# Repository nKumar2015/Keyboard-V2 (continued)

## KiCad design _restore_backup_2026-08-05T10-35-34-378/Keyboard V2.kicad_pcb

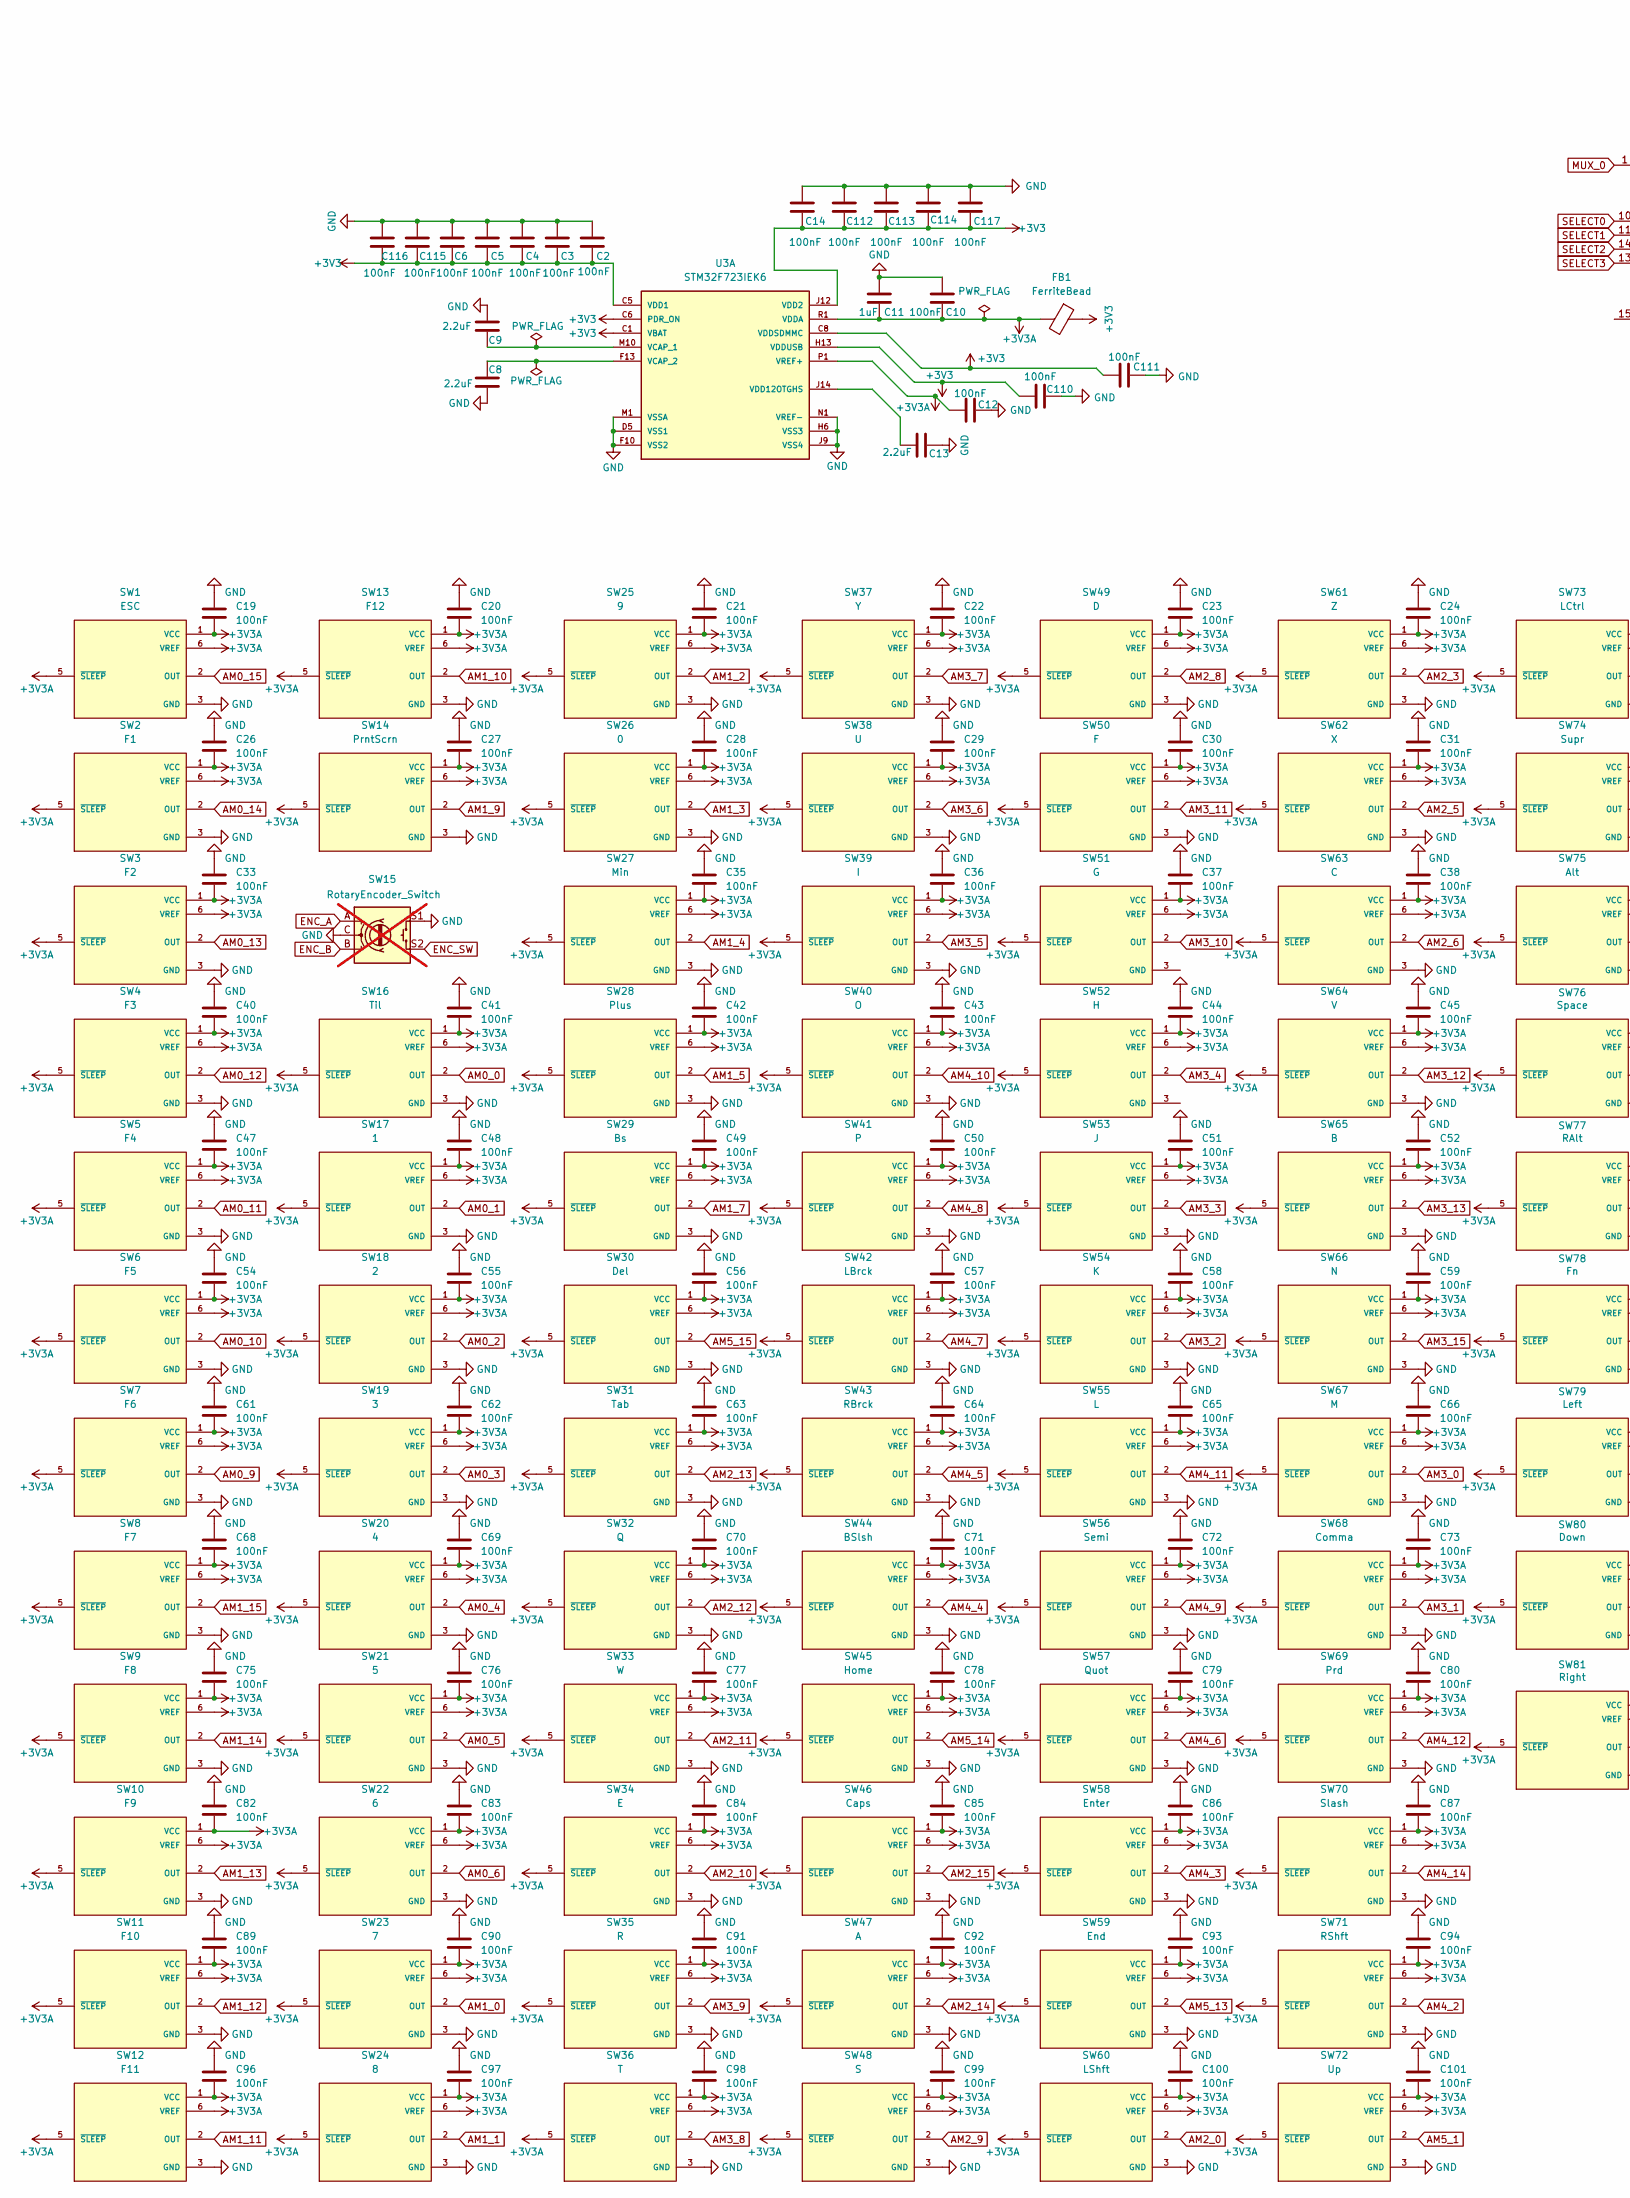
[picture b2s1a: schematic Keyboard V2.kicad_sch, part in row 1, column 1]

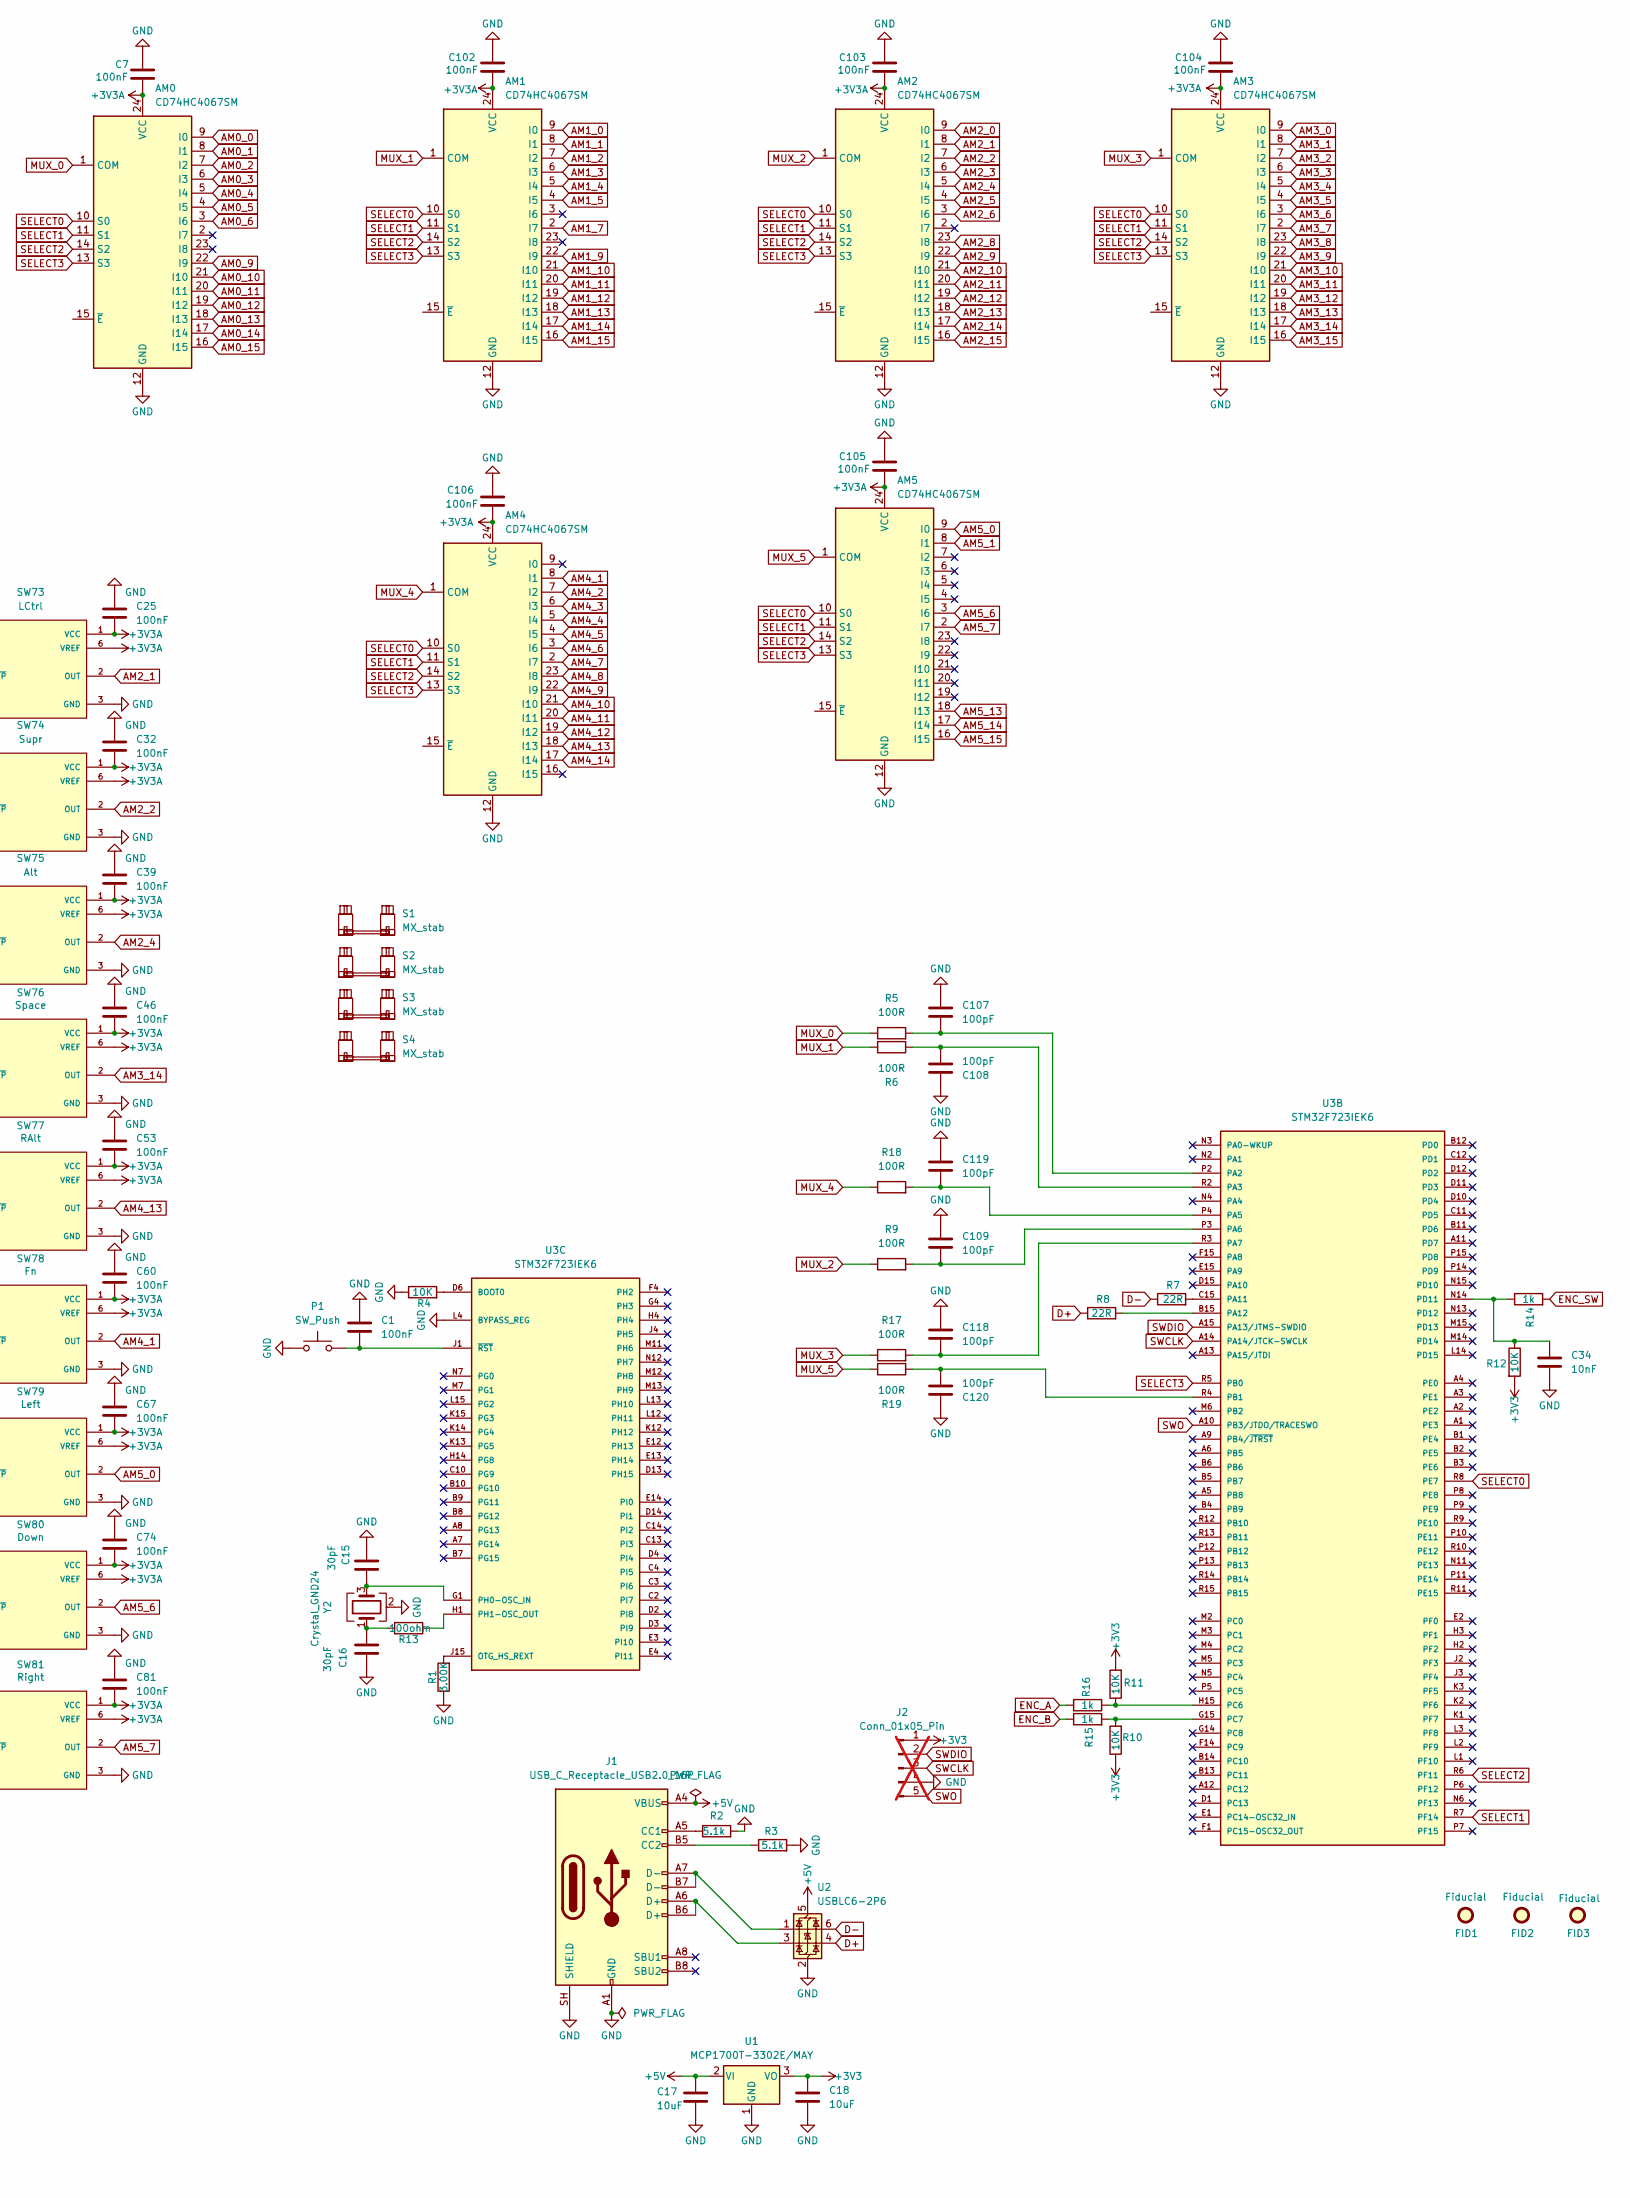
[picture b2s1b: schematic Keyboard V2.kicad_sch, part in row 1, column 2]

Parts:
AM0, AM1, AM2, AM3, AM4, AM5: CD74HC4067SM; SSOP-24_5.3x8.2mm_P0.65mm; LCSC C98457
C1, C7, C102, C103, C104, C105, C106: 100nF; C_0603_1608Metric
C2, C3, C4, C5, C6, C10, C12, C14, C19, C20, C21, C22, C23, C24, C25, C26, C27, C28, C29, C30, C31, C32, C33, C35, C36, C37, C38, C39, C40, C41, C42, C43, C44, C45, C46, C47, C48, C49, C50, C51, C52, C53, C54, C55, C56, C57, C58, C59, C60, C61, C62, C63, C64, C65, C66, C67, C68, C69, C70, C71, C72, C73, C74, C75, C76, C77, C78, C79, C80, C81, C82, C83, C84, C85, C86, C87, C89, C90, C91, C92, C93, C94, C96, C97, C98, C99, C100, C101, C110, C111, C112, C113, C114, C115, C116, C117: 100nF; C_0402_1005Metric
C8, C9, C13: 2.2uF; C_0402_1005Metric
C11: 1uF; C_0402_1005Metric
C15, C16: 30pF; C_0402_1005Metric
C17, C18: 10uF; C_0805_2012Metric
C34: 10nF; C_0402_1005Metric
C107, C108, C109, C118, C119, C120: 100pF; C_0402_1005Metric
FB1: FerriteBead; L_0603_1608Metric
FID1, FID2, FID3: Fiducial; Fiducial_1mm_Mask2mm
J1: USB_C_Receptacle_USB2.0_16P; USB_C_Receptacle_HRO_TYPE-C-31-M-12
J2: Conn_01x05_Pin; PinHeader_1x05_P2.54mm_Horizontal; not fitted
P1: SW_Push; SW_SPST_SKQG_WithStem
R1: 3.00K; R_0603_1608Metric
R2, R3: 5.1k; R_0603_1608Metric
R4, R12: 10K; R_0603_1608Metric
R5, R6, R9, R17, R18, R19: 100R; R_0402_1005Metric
R7, R8: 22R; R_0402_1005Metric
R10, R11: 10K; R_0402_1005Metric
R13: 100ohm; R_0603_1608Metric
R14: 1k; R_0603_1608Metric
R15, R16: 1k; R_0402_1005Metric
S1: MX_stab; STAB_MX_P_6.25u
S2: MX_stab; STAB_MX_2.25u
S3: MX_stab; STAB_MX_P_2.25u
S4: MX_stab; STAB_MX_P_2u
SW1: ESC; SW_MX_HE_0deg_1u_DFN; PARTREV 7; LCSC C146410
SW2: F1; SW_MX_HE_0deg_1u_DFN; PARTREV 7; LCSC C146410
SW3: F2; SW_MX_HE_0deg_1u_DFN; PARTREV 7; LCSC C146410
SW4: F3; SW_MX_HE_0deg_1u_DFN; PARTREV 7; LCSC C146410
SW5: F4; SW_MX_HE_0deg_1u_DFN; PARTREV 7; LCSC C146410
SW6: F5; SW_MX_HE_0deg_1u_DFN; PARTREV 7; LCSC C146410
SW7: F6; SW_MX_HE_0deg_1u_DFN; PARTREV 7; LCSC C146410
SW8: F7; SW_MX_HE_0deg_1u_DFN; PARTREV 7; LCSC C146410
SW9: F8; SW_MX_HE_0deg_1u_DFN; PARTREV 7; LCSC C146410
SW10: F9; SW_MX_HE_0deg_1u_DFN; PARTREV 7; LCSC C146410
SW11: F10; SW_MX_HE_0deg_1u_DFN; PARTREV 7; LCSC C146410
SW12: F11; SW_MX_HE_0deg_1u_DFN; PARTREV 7; LCSC C146410
SW13: F12; SW_MX_HE_0deg_1u_DFN; PARTREV 7; LCSC C146410
SW14: PrntScrn; SW_MX_HE_0deg_1u_DFN; PARTREV 7; LCSC C146410
SW15: RotaryEncoder_Switch; ROT_Alps_EC11E-Switch; not fitted
SW16: Til; SW_MX_HE_0deg_1u_DFN; PARTREV 7; LCSC C146410
SW17: 1; SW_MX_HE_0deg_1u_DFN; PARTREV 7; LCSC C146410
SW18: 2; SW_MX_HE_0deg_1u_DFN; PARTREV 7; LCSC C146410
SW19: 3; SW_MX_HE_0deg_1u_DFN; PARTREV 7; LCSC C146410
SW20: 4; SW_MX_HE_0deg_1u_DFN; PARTREV 7; LCSC C146410
SW21: 5; SW_MX_HE_0deg_1u_DFN; PARTREV 7; LCSC C146410
SW22: 6; SW_MX_HE_0deg_1u_DFN; PARTREV 7; LCSC C146410
SW23: 7; SW_MX_HE_0deg_1u_DFN; PARTREV 7; LCSC C146410
SW24: 8; SW_MX_HE_0deg_1u_DFN; PARTREV 7; LCSC C146410
SW25: 9; SW_MX_HE_0deg_1u_DFN; PARTREV 7; LCSC C146410
SW26: 0; SW_MX_HE_0deg_1u_DFN; PARTREV 7; LCSC C146410
SW27: Min; SW_MX_HE_0deg_1u_DFN; PARTREV 7; LCSC C146410
SW28: Plus; SW_MX_HE_0deg_1u_DFN; PARTREV 7; LCSC C146410
SW29: Bs; SW_MX_HE_0deg_1u_DFN; PARTREV 7; LCSC C146410
SW30: Del; SW_MX_HE_0deg_1u_DFN; PARTREV 7; LCSC C146410
SW31: Tab; SW_MX_HE_0deg_1u_DFN; PARTREV 7; LCSC C146410
SW32: Q; SW_MX_HE_0deg_1u_DFN; PARTREV 7; LCSC C146410
SW33: W; SW_MX_HE_0deg_1u_DFN; PARTREV 7; LCSC C146410
SW34: E; SW_MX_HE_0deg_1u_DFN; PARTREV 7; LCSC C146410
SW35: R; SW_MX_HE_0deg_1u_DFN; PARTREV 7; LCSC C146410
SW36: T; SW_MX_HE_0deg_1u_DFN; PARTREV 7; LCSC C146410
SW37: Y; SW_MX_HE_0deg_1u_DFN; PARTREV 7; LCSC C146410
SW38: U; SW_MX_HE_0deg_1u_DFN; PARTREV 7; LCSC C146410
SW39: I; SW_MX_HE_0deg_1u_DFN; PARTREV 7; LCSC C146410
SW40: O; SW_MX_HE_0deg_1u_DFN; PARTREV 7; LCSC C146410
SW41: P; SW_MX_HE_0deg_1u_DFN; PARTREV 7; LCSC C146410
SW42: LBrck; SW_MX_HE_0deg_1u_DFN; PARTREV 7; LCSC C146410
SW43: RBrck; SW_MX_HE_0deg_1u_DFN; PARTREV 7; LCSC C146410
SW44: BSlsh; SW_MX_HE_0deg_1u_DFN; PARTREV 7; LCSC C146410
SW45: Home; SW_MX_HE_0deg_1u_DFN; PARTREV 7; LCSC C146410
SW46: Caps; SW_MX_HE_0deg_1u_DFN; PARTREV 7; LCSC C146410
SW47: A; SW_MX_HE_0deg_1u_DFN; PARTREV 7; LCSC C146410
SW48: S; SW_MX_HE_0deg_1u_DFN; PARTREV 7; LCSC C146410
SW49: D; SW_MX_HE_0deg_1u_DFN; PARTREV 7; LCSC C146410
SW50: F; SW_MX_HE_0deg_1u_DFN; PARTREV 7; LCSC C146410
SW51: G; SW_MX_HE_0deg_1u_DFN; PARTREV 7; LCSC C146410
SW52: H; SW_MX_HE_0deg_1u_DFN; PARTREV 7; LCSC C146410
SW53: J; SW_MX_HE_0deg_1u_DFN; PARTREV 7; LCSC C146410
SW54: K; SW_MX_HE_0deg_1u_DFN; PARTREV 7; LCSC C146410
SW55: L; SW_MX_HE_0deg_1u_DFN; PARTREV 7; LCSC C146410
SW56: Semi; SW_MX_HE_0deg_1u_DFN; PARTREV 7; LCSC C146410
SW57: Quot; SW_MX_HE_0deg_1u_DFN; PARTREV 7; LCSC C146410
SW58: Enter; SW_MX_HE_0deg_1u_DFN; PARTREV 7; LCSC C146410
SW59: End; SW_MX_HE_0deg_1u_DFN; PARTREV 7; LCSC C146410
SW60: LShft; SW_MX_HE_0deg_1u_DFN; PARTREV 7; LCSC C146410
SW61: Z; SW_MX_HE_0deg_1u_DFN; PARTREV 7; LCSC C146410
SW62: X; SW_MX_HE_0deg_1u_DFN; PARTREV 7; LCSC C146410
SW63: C; SW_MX_HE_0deg_1u_DFN; PARTREV 7; LCSC C146410
SW64: V; SW_MX_HE_0deg_1u_DFN; PARTREV 7; LCSC C146410
SW65: B; SW_MX_HE_0deg_1u_DFN; PARTREV 7; LCSC C146410
SW66: N; SW_MX_HE_0deg_1u_DFN; PARTREV 7; LCSC C146410
SW67: M; SW_MX_HE_0deg_1u_DFN; PARTREV 7; LCSC C146410
SW68: Comma; SW_MX_HE_0deg_1u_DFN; PARTREV 7; LCSC C146410
SW69: Prd; SW_MX_HE_0deg_1u_DFN; PARTREV 7; LCSC C146410
SW70: Slash; SW_MX_HE_0deg_1u_DFN; PARTREV 7; LCSC C146410
SW71: RShft; SW_MX_HE_0deg_1u_DFN; PARTREV 7; LCSC C146410
SW72: Up; SW_MX_HE_0deg_1u_DFN; PARTREV 7; LCSC C146410
SW73: LCtrl; SW_MX_HE_0deg_1u_DFN; PARTREV 7; LCSC C146410
SW74: Supr; SW_MX_HE_0deg_1u_DFN; PARTREV 7; LCSC C146410
SW75: Alt; SW_MX_HE_0deg_1u_DFN; PARTREV 7; LCSC C146410
SW76: Space; SW_MX_HE_0deg_1u_DFN; PARTREV 7; LCSC C146410
SW77: RAlt; SW_MX_HE_0deg_1u_DFN; PARTREV 7; LCSC C146410
SW78: Fn; SW_MX_HE_0deg_1u_DFN; PARTREV 7; LCSC C146410
SW79: Left; SW_MX_HE_0deg_1u_DFN; PARTREV 7; LCSC C146410
SW80: Down; SW_MX_HE_0deg_1u_DFN; PARTREV 7; LCSC C146410
SW81: Right; SW_MX_HE_0deg_1u_DFN; PARTREV 7; LCSC C146410
U1: MCP1700T-3302E/MAY; DFN-6-1EP_2x2mm_P0.65mm_EP1x1.6mm
U2: USBLC6-2P6; SOT-666
U3: STM32F723IEK6; IC_STM32F723IEK6; PARTREV 9
Y2: Crystal_GND24; Crystal_SMD_Abracon_ABM8G-4Pin_3.2x2.5mm

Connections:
+3V3: C2.1, C3.2, C4.2, C5.2, C6.2, C14.1, C18.1, C110.2, C111.1, C112.1, C113.1, C114.1, C115.2, C116.1, C117.1, FB1.1, J2.1, R10.1, R11.2, R12.2, U1.3 (VO), U3.C1 (VBAT), U3.C5 (VDD1), U3.C6 (PDR_ON), U3.C7 (VDD1), U3.C8 (VDDSDMMC), U3.C9 (VDD1), U3.F3 (VDD1), U3.G3 (VDD1), U3.G13 (VDD1), U3.H13 (VDDUSB), U3.J12 (VDD2), U3.J13 (VDD2), U3.K4 (VDD2), U3.N8 (VDD2), U3.N9 (VDD2), U3.N10 (VDD2)
+3V3A: AM0.24 (VCC), AM1.24 (VCC), AM2.24 (VCC), AM3.24 (VCC), AM4.24 (VCC), AM5.24 (VCC), C7.2, C10.2, C11.2, C12.2, C19.2, C20.2, C21.2, C22.2, C23.2, C24.2, C25.2, C26.2, C27.2, C28.2, C29.2, C30.2, C31.2, C32.2, C33.2, C35.2, C36.2, C37.2, C38.2, C39.2, C40.2, C41.2, C42.2, C43.2, C44.2, C45.2, C46.2, C47.2, C48.2, C49.2, C50.2, C51.2, C52.2, C53.2, C54.2, C55.2, C56.2, C57.2, C58.2, C59.2, C60.2, C61.2, C62.2, C63.2, C64.2, C65.2, C66.2, C67.2, C68.2, C69.2, C70.2, C71.2, C72.2, C73.2, C74.2, C75.2, C76.2, C77.2, C78.2, C79.2, C80.2, C81.2, C82.2, C83.2, C84.2, C85.2, C86.2, C87.2, C89.2, C90.2, C91.2, C92.2, C93.2, C94.2, C96.2, C97.2, C98.2, C99.2, C100.2, C101.2, C102.2, C103.2, C104.2, C105.2, C106.2, FB1.2, SW1.1 (VCC), SW1.5 (~SLEEP), SW1.6 (VREF), SW2.1 (VCC), SW2.5 (~SLEEP), SW2.6 (VREF), SW3.1 (VCC), SW3.5 (~SLEEP), SW3.6 (VREF), SW4.1 (VCC), SW4.5 (~SLEEP), SW4.6 (VREF), SW5.1 (VCC), SW5.5 (~SLEEP), SW5.6 (VREF), SW6.1 (VCC), SW6.5 (~SLEEP), SW6.6 (VREF), SW7.1 (VCC), SW7.5 (~SLEEP), SW7.6 (VREF), SW8.1 (VCC), SW8.5 (~SLEEP), SW8.6 (VREF), SW9.1 (VCC), SW9.5 (~SLEEP), SW9.6 (VREF), SW10.1 (VCC), SW10.5 (~SLEEP), SW10.6 (VREF), SW11.1 (VCC), SW11.5 (~SLEEP), SW11.6 (VREF), SW12.1 (VCC), SW12.5 (~SLEEP), SW12.6 (VREF), SW13.1 (VCC), SW13.5 (~SLEEP), SW13.6 (VREF), SW14.1 (VCC), SW14.5 (~SLEEP), SW14.6 (VREF), SW16.1 (VCC), SW16.5 (~SLEEP), SW16.6 (VREF), SW17.1 (VCC), SW17.5 (~SLEEP), SW17.6 (VREF), SW18.1 (VCC), SW18.5 (~SLEEP), SW18.6 (VREF), SW19.1 (VCC), SW19.5 (~SLEEP), SW19.6 (VREF), SW20.1 (VCC), SW20.5 (~SLEEP), SW20.6 (VREF), SW21.1 (VCC), SW21.5 (~SLEEP), SW21.6 (VREF), SW22.1 (VCC), SW22.5 (~SLEEP), SW22.6 (VREF), SW23.1 (VCC), SW23.5 (~SLEEP), SW23.6 (VREF), SW24.1 (VCC), SW24.5 (~SLEEP), SW24.6 (VREF), SW25.1 (VCC), SW25.5 (~SLEEP), SW25.6 (VREF), SW26.1 (VCC), SW26.5 (~SLEEP), SW26.6 (VREF), SW27.1 (VCC), SW27.5 (~SLEEP), SW27.6 (VREF), SW28.1 (VCC), SW28.5 (~SLEEP), SW28.6 (VREF), SW29.1 (VCC), SW29.5 (~SLEEP), SW29.6 (VREF), SW30.1 (VCC), SW30.5 (~SLEEP), SW30.6 (VREF), SW31.1 (VCC), SW31.5 (~SLEEP), SW31.6 (VREF), SW32.1 (VCC), SW32.5 (~SLEEP), SW32.6 (VREF), SW33.1 (VCC), SW33.5 (~SLEEP), SW33.6 (VREF), SW34.1 (VCC), SW34.5 (~SLEEP), SW34.6 (VREF), SW35.1 (VCC), SW35.5 (~SLEEP), SW35.6 (VREF), SW36.1 (VCC), SW36.5 (~SLEEP), SW36.6 (VREF), SW37.1 (VCC), SW37.5 (~SLEEP), SW37.6 (VREF), SW38.1 (VCC), SW38.5 (~SLEEP), SW38.6 (VREF), SW39.1 (VCC), SW39.5 (~SLEEP), SW39.6 (VREF), SW40.1 (VCC), SW40.5 (~SLEEP), SW40.6 (VREF), SW41.1 (VCC), SW41.5 (~SLEEP), SW41.6 (VREF), SW42.1 (VCC), SW42.5 (~SLEEP), SW42.6 (VREF), SW43.1 (VCC), SW43.5 (~SLEEP), SW43.6 (VREF), SW44.1 (VCC), SW44.5 (~SLEEP), SW44.6 (VREF), SW45.1 (VCC), SW45.5 (~SLEEP), SW45.6 (VREF), SW46.1 (VCC), SW46.5 (~SLEEP), SW46.6 (VREF), SW47.1 (VCC), SW47.5 (~SLEEP), SW47.6 (VREF), SW48.1 (VCC), SW48.5 (~SLEEP), SW48.6 (VREF), SW49.1 (VCC), SW49.5 (~SLEEP), SW49.6 (VREF), SW50.1 (VCC), SW50.5 (~SLEEP), SW50.6 (VREF), SW51.1 (VCC), SW51.5 (~SLEEP), SW51.6 (VREF), SW52.1 (VCC), SW52.5 (~SLEEP), SW52.6 (VREF), SW53.1 (VCC), SW53.5 (~SLEEP), SW53.6 (VREF), SW54.1 (VCC), SW54.5 (~SLEEP), SW54.6 (VREF), SW55.1 (VCC), SW55.5 (~SLEEP), SW55.6 (VREF), SW56.1 (VCC), SW56.5 (~SLEEP), SW56.6 (VREF), SW57.1 (VCC), SW57.5 (~SLEEP), SW57.6 (VREF), SW58.1 (VCC), SW58.5 (~SLEEP), SW58.6 (VREF), SW59.1 (VCC), SW59.5 (~SLEEP), SW59.6 (VREF), SW60.1 (VCC), SW60.5 (~SLEEP), SW60.6 (VREF), SW61.1 (VCC), SW61.5 (~SLEEP), SW61.6 (VREF), SW62.1 (VCC), SW62.5 (~SLEEP), SW62.6 (VREF), SW63.1 (VCC), SW63.5 (~SLEEP), SW63.6 (VREF), SW64.1 (VCC), SW64.5 (~SLEEP), SW64.6 (VREF), SW65.1 (VCC), SW65.5 (~SLEEP), SW65.6 (VREF), SW66.1 (VCC), SW66.5 (~SLEEP), SW66.6 (VREF), SW67.1 (VCC), SW67.5 (~SLEEP), SW67.6 (VREF), SW68.1 (VCC), SW68.5 (~SLEEP), SW68.6 (VREF), SW69.1 (VCC), SW69.5 (~SLEEP), SW69.6 (VREF), SW70.1 (VCC), SW70.5 (~SLEEP), SW70.6 (VREF), SW71.1 (VCC), SW71.5 (~SLEEP), SW71.6 (VREF), SW72.1 (VCC), SW72.5 (~SLEEP), SW72.6 (VREF), SW73.1 (VCC), SW73.5 (~SLEEP), SW73.6 (VREF), SW74.1 (VCC), SW74.5 (~SLEEP), SW74.6 (VREF), SW75.1 (VCC), SW75.5 (~SLEEP), SW75.6 (VREF), SW76.1 (VCC), SW76.5 (~SLEEP), SW76.6 (VREF), SW77.1 (VCC), SW77.5 (~SLEEP), SW77.6 (VREF), SW78.1 (VCC), SW78.5 (~SLEEP), SW78.6 (VREF), SW79.1 (VCC), SW79.5 (~SLEEP), SW79.6 (VREF), SW80.1 (VCC), SW80.5 (~SLEEP), SW80.6 (VREF), SW81.1 (VCC), SW81.5 (~SLEEP), SW81.6 (VREF), U3.P1 (VREF+), U3.R1 (VDDA)
+5V: C17.1, J1.A4 (VBUS), J1.A9 (VBUS), J1.B4 (VBUS), J1.B9 (VBUS), U1.2 (VI), U2.5 (VBUS)
AM0_0: AM0.9 (I0), SW16.2 (OUT)
AM0_1: AM0.8 (I1), SW17.2 (OUT)
AM0_2: AM0.7 (I2), SW18.2 (OUT)
AM0_3: AM0.6 (I3), SW19.2 (OUT)
AM0_4: AM0.5 (I4), SW20.2 (OUT)
AM0_5: AM0.4 (I5), SW21.2 (OUT)
AM0_6: AM0.3 (I6), SW22.2 (OUT)
AM0_9: AM0.22 (I9), SW7.2 (OUT)
AM0_10: AM0.21 (I10), SW6.2 (OUT)
AM0_11: AM0.20 (I11), SW5.2 (OUT)
AM0_12: AM0.19 (I12), SW4.2 (OUT)
AM0_13: AM0.18 (I13), SW3.2 (OUT)
AM0_14: AM0.17 (I14), SW2.2 (OUT)
AM0_15: AM0.16 (I15), SW1.2 (OUT)
AM1_0: AM1.9 (I0), SW23.2 (OUT)
AM1_1: AM1.8 (I1), SW24.2 (OUT)
AM1_2: AM1.7 (I2), SW25.2 (OUT)
AM1_3: AM1.6 (I3), SW26.2 (OUT)
AM1_4: AM1.5 (I4), SW27.2 (OUT)
AM1_5: AM1.4 (I5), SW28.2 (OUT)
AM1_7: AM1.2 (I7), SW29.2 (OUT)
AM1_9: AM1.22 (I9), SW14.2 (OUT)
AM1_10: AM1.21 (I10), SW13.2 (OUT)
AM1_11: AM1.20 (I11), SW12.2 (OUT)
AM1_12: AM1.19 (I12), SW11.2 (OUT)
AM1_13: AM1.18 (I13), SW10.2 (OUT)
AM1_14: AM1.17 (I14), SW9.2 (OUT)
AM1_15: AM1.16 (I15), SW8.2 (OUT)
AM2_0: AM2.9 (I0), SW60.2 (OUT)
AM2_1: AM2.8 (I1), SW73.2 (OUT)
AM2_2: AM2.7 (I2), SW74.2 (OUT)
AM2_3: AM2.6 (I3), SW61.2 (OUT)
AM2_4: AM2.5 (I4), SW75.2 (OUT)
AM2_5: AM2.4 (I5), SW62.2 (OUT)
AM2_6: AM2.3 (I6), SW63.2 (OUT)
AM2_8: AM2.23 (I8), SW49.2 (OUT)
AM2_9: AM2.22 (I9), SW48.2 (OUT)
AM2_10: AM2.21 (I10), SW34.2 (OUT)
AM2_11: AM2.20 (I11), SW33.2 (OUT)
AM2_12: AM2.19 (I12), SW32.2 (OUT)
AM2_13: AM2.18 (I13), SW31.2 (OUT)
AM2_14: AM2.17 (I14), SW47.2 (OUT)
AM2_15: AM2.16 (I15), SW46.2 (OUT)
AM3_0: AM3.9 (I0), SW67.2 (OUT)
AM3_1: AM3.8 (I1), SW68.2 (OUT)
AM3_2: AM3.7 (I2), SW54.2 (OUT)
AM3_3: AM3.6 (I3), SW53.2 (OUT)
AM3_4: AM3.5 (I4), SW52.2 (OUT)
AM3_5: AM3.4 (I5), SW39.2 (OUT)
AM3_6: AM3.3 (I6), SW38.2 (OUT)
AM3_7: AM3.2 (I7), SW37.2 (OUT)
AM3_8: AM3.23 (I8), SW36.2 (OUT)
AM3_9: AM3.22 (I9), SW35.2 (OUT)
AM3_10: AM3.21 (I10), SW51.2 (OUT)
AM3_11: AM3.20 (I11), SW50.2 (OUT)
AM3_12: AM3.19 (I12), SW64.2 (OUT)
AM3_13: AM3.18 (I13), SW65.2 (OUT)
AM3_14: AM3.17 (I14), SW76.2 (OUT)
AM3_15: AM3.16 (I15), SW66.2 (OUT)
AM4_1: AM4.8 (I1), SW78.2 (OUT)
AM4_2: AM4.7 (I2), SW71.2 (OUT)
AM4_3: AM4.6 (I3), SW58.2 (OUT)
AM4_4: AM4.5 (I4), SW44.2 (OUT)
AM4_5: AM4.4 (I5), SW43.2 (OUT)
AM4_6: AM4.3 (I6), SW57.2 (OUT)
AM4_7: AM4.2 (I7), SW42.2 (OUT)
AM4_8: AM4.23 (I8), SW41.2 (OUT)
AM4_9: AM4.22 (I9), SW56.2 (OUT)
AM4_10: AM4.21 (I10), SW40.2 (OUT)
AM4_11: AM4.20 (I11), SW55.2 (OUT)
AM4_12: AM4.19 (I12), SW69.2 (OUT)
AM4_13: AM4.18 (I13), SW77.2 (OUT)
AM4_14: AM4.17 (I14), SW70.2 (OUT)
AM5_0: AM5.9 (I0), SW79.2 (OUT)
AM5_1: AM5.8 (I1), SW72.2 (OUT)
AM5_6: AM5.3 (I6), SW80.2 (OUT)
AM5_7: AM5.2 (I7), SW81.2 (OUT)
AM5_13: AM5.18 (I13), SW59.2 (OUT)
AM5_14: AM5.17 (I14), SW45.2 (OUT)
AM5_15: AM5.16 (I15), SW30.2 (OUT)
D+: R8.1, U2.4 (I/O2)
D-: R7.1, U2.6 (I/O1)
ENC_A: R16.2, SW15.A
ENC_B: R15.1, SW15.B
ENC_SW: R14.2, SW15.S2
MUX_0: AM0.1 (COM), R5.1
MUX_1: AM1.1 (COM), R6.1
MUX_2: AM2.1 (COM), R9.1
MUX_3: AM3.1 (COM), R17.1
MUX_4: AM4.1 (COM), R18.1
MUX_5: AM5.1 (COM), R19.1
unnamed: C16.1, R13.2, Y2.1
unnamed: J1.A5 (CC1), R2.1
unnamed: J1.B5 (CC2), R3.1
unnamed: J1.A6 (D+), J1.B6 (D+), U2.3 (I/O2)
unnamed: J1.A7 (D-), J1.B7 (D-), U2.1 (I/O1)
unnamed: C9.1, U3.M10 (VCAP_1)
unnamed: C8.2, U3.F13 (VCAP_2)
unnamed: C13.2, U3.J14 (VDD12OTGHS)
unnamed: C107.2, R5.2, U3.P2 (PA2)
unnamed: C108.2, R6.2, U3.R2 (PA3)
unnamed: C119.2, R18.2, U3.P4 (PA5)
unnamed: C109.2, R9.2, U3.P3 (PA6)
unnamed: C118.2, R17.2, U3.R3 (PA7)
unnamed: R7.2, U3.C15 (PA11)
unnamed: R8.2, U3.B15 (PA12)
unnamed: C120.2, R19.2, U3.R4 (PB1)
unnamed: R11.1, R16.1, U3.H15 (PC6)
unnamed: R10.2, R15.2, U3.G15 (PC7)
unnamed: C34.1, R12.1, R14.1, U3.N14 (PD11)
unnamed: R4.2, U3.D6 (BOOT0)
unnamed: R1.2, U3.J15 (OTG_HS_REXT)
unnamed: C15.1, U3.G1 (PH0-OSC_IN), Y2.3
unnamed: R13.1, U3.H1 (PH1-OSC_OUT)
unnamed: C1.2, P1.2, U3.J1 (~RST)
SELECT0: AM0.10 (S0), AM1.10 (S0), AM2.10 (S0), AM3.10 (S0), AM4.10 (S0), AM5.10 (S0), U3.R8 (PE7)
SELECT1: AM0.11 (S1), AM1.11 (S1), AM2.11 (S1), AM3.11 (S1), AM4.11 (S1), AM5.11 (S1), U3.R7 (PF14)
SELECT2: AM0.14 (S2), AM1.14 (S2), AM2.14 (S2), AM3.14 (S2), AM4.14 (S2), AM5.14 (S2), U3.R6 (PF11)
SELECT3: AM0.13 (S3), AM1.13 (S3), AM2.13 (S3), AM3.13 (S3), AM4.13 (S3), AM5.13 (S3), U3.R5 (PB0)
SWCLK: J2.3, U3.A14 (PA14/JTCK-SWCLK)
SWDIO: J2.2, U3.A15 (PA13/JTMS-SWDIO)
SWO: J2.5, U3.A10 (PB3/JTDO/TRACESWO)

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
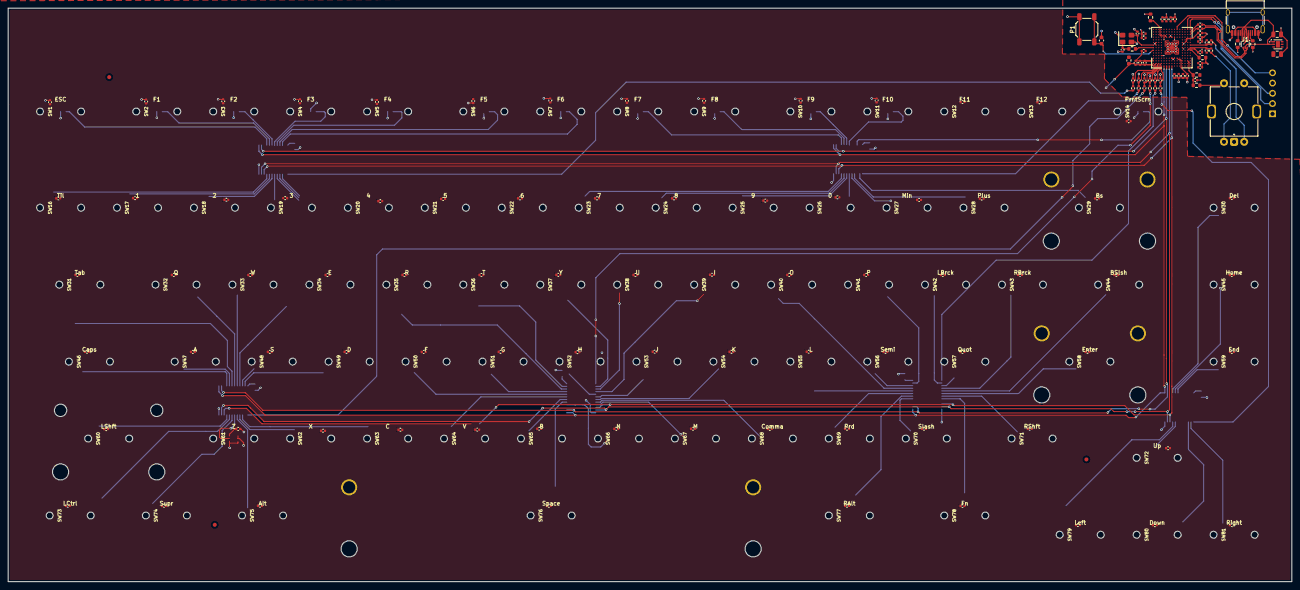
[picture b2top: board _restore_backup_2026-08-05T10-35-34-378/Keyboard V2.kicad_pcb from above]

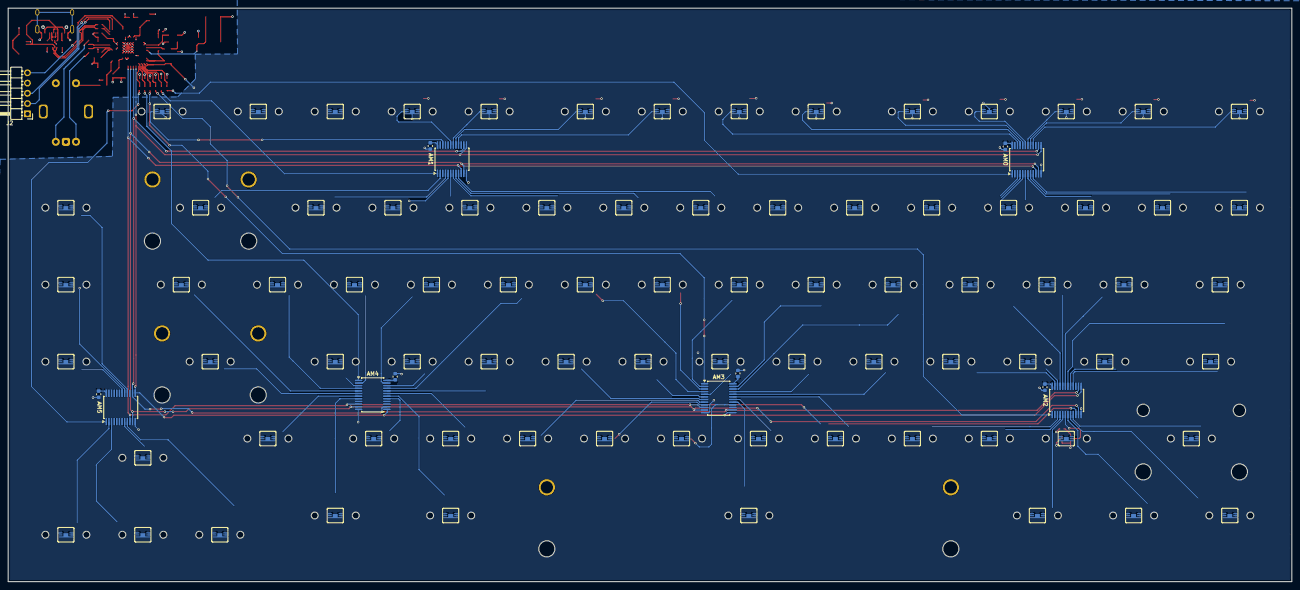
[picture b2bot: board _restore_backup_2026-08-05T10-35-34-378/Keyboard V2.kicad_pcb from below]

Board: 4 copper layers, 317.8 x 142.0 mm, 239 parts (13 on the bottom side), 126 nets.
